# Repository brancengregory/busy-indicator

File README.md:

# Busy Indicator

A wireless status indicator system built with the XIAO ESP32C3. Designed for pairs who want to communicate their availability without interrupting each other's flow state.

## Overview

The Busy Indicator is a simple, elegant solution to a common problem: knowing when your partner or colleague is available without the social pressure of asking. Each device has two sets of red/green LEDs:

- **Local LEDs**: Show your current status (controlled by you)
- **Remote LEDs**: Show your partner's status (received wirelessly)

When your partner presses their button to change status, your remote LEDs update automatically via ESP-NOW wireless communication.

## Features

- **Dual Status Display**: Four LEDs total - two for your status, two for your partner's
- **Simple Controls**: Single button press toggles your status (red = busy, green = available)
- **Sleep Mode**: Long press (2 seconds) to enter light sleep for power saving
- **Wake on Button**: Press button to wake from sleep and resume operation
- **Wireless Sync**: ESP-NOW protocol provides instant status updates between devices
- **Visual Feedback**: Amber blinking confirms long press and wake events
- **Debounced Input**: Reliable button detection with 50ms debounce
- **Power Efficient**: Light sleep mode consumes minimal power when not in use

## Hardware

The PCB is designed around the Seeed Studio XIAO ESP32C3 with:

- **Microcontroller**: XIAO ESP32C3 (RISC-V, WiFi + Bluetooth)
- **LEDs**: 4x 3mm through-hole LEDs (2 red, 2 green)
- **Current limiting**: 4x axial resistors
- **Input**: 12mm push button
- **Power**: USB-C via XIAO board (or external battery via battery pads)

### GPIO Pinout

| Function | GPIO |
|----------|------|
| Local Red LED | GPIO3 |
| Local Green LED | GPIO4 |
| Remote Red LED | GPIO21 |
| Remote Green LED | GPIO20 |
| Button | GPIO10 |

### PCB Design Files

The hardware design is in KiCad 9.0 format:

- `hardware/busy-indicator/busy-indicator.kicad_sch` - Schematic
- `hardware/busy-indicator/busy-indicator.kicad_pcb` - PCB layout
- `hardware/busy-indicator/busy-indicator.kicad_pro` - Project settings
- `hardware/libs/XIAO_ESP32C3/` - XIAO ESP32C3 footprint and symbol library (git submodule)

## Firmware

The firmware is written in Rust using the Embassy async framework:

- **Language**: Rust (embedded no-std)
- **Framework**: Embassy (async/await for embedded)
- **HAL**: esp-hal for ESP32-C3
- **Networking**: esp-radio (ESP-NOW over WiFi)
- **Target**: riscv32imc-unknown-none-elf

### Architecture

The firmware uses an actor-model architecture with Embassy tasks:

1. **State Manager** (`state_manager`): Pure state machine handling all state transitions
2. **LED Controller** (`led_controller`): Handles LED output with retry logic
3. **Button Task** (`button_task`): Button debouncing, press detection, and sleep control
4. **ESP-NOW Task** (`esp_now_task`): Wireless communication between devices

### Key Components

- **ButtonHandler**: Debounced button input with short/long press detection
- **LedPair**: Abstraction for red/green LED pairs with color mixing (red + green = amber)
- **SystemState**: Tracks local status, remote status, and sleep state
- **Pure Transitions**: State changes are pure functions (no side effects), making testing easy

## Building

### Prerequisites

- Rust toolchain with `riscv32imc-unknown-none-elf` target
- `espflash` or `cargo-espflash` for flashing
- KiCad 9.0+ (for hardware modifications)

### Flashing Firmware

```bash
# Build and flash
cargo run --release

# Or flash pre-built binary
espflash flash target/riscv32imc-unknown-none-elf/release/busy-indicator
```

### Hardware Manufacturing

1. Open `hardware/busy-indicator/busy-indicator.kicad_pcb` in KiCad
2. Generate Gerber files for fabrication
3. Order PCBs from your preferred manufacturer (JLCPCB, PCBWay, etc.)
4. Solder components according to the schematic

## Usage

1. **Power on**: Both LED pairs will blink amber 3 times, then show red (default busy state)
2. **Toggle status**: Short press the button to switch between red (busy) and green (available)
3. **Check partner status**: Look at the "remote" LED pair - it mirrors your partner's device
4. **Enter sleep**: Long press the button (hold for 2 seconds until LEDs blink) to enter low-power mode
5. **Wake up**: Press the button to wake from sleep - LEDs will blink amber to confirm

### Wireless Pairing

Devices automatically discover each other via ESP-NOW broadcast on channel 11. No manual pairing required - just power on two devices within range and they'll sync automatically.

## Project Structure

```
busy-indicator/
├── src/
│   ├── bin/main.rs       # Firmware entry point and task definitions
│   └── lib.rs            # Library (currently empty, no_std marker)
├── hardware/
│   ├── busy-indicator/   # KiCad PCB design files
│   └── libs/             # Component libraries (XIAO_ESP32C3 submodule)
├── Cargo.toml            # Rust dependencies
├── build.rs              # Build script with helpful linker errors
└── .gitignore            # Git ignore patterns for Rust + KiCad
```

## License

This project is open source. See individual component licenses:
- Firmware: See LICENSE file in repository root
- XIAO_ESP32C3 library: See `hardware/libs/XIAO_ESP32C3/LICENSE`

## Acknowledgments

- [esp-hal](https://github.com/esp-rs/esp-hal) - Rust HAL for ESP microcontrollers
- [Embassy](https://github.com/embassy-rs/embassy) - Async/await framework for embedded
- [esp-radio](https://github.com/esp-rs/esp-radio) - WiFi/ESP-NOW support for ESP32
- [Seeed Studio](https://www.seeedstudio.com/) - XIAO ESP32C3 hardware

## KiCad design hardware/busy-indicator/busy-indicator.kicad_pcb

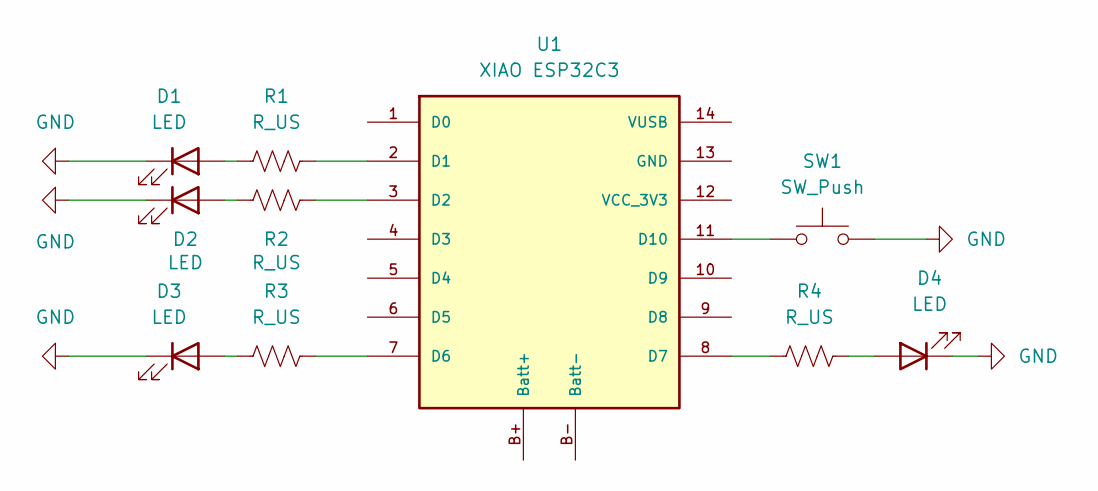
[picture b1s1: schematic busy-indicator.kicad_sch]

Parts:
D1, D2, D3, D4: LED; LED_D3.0mm
R1, R2, R3, R4: R_US; R_Axial_DIN0207_L6.3mm_D2.5mm_P10.16mm_Horizontal
SW1: SW_Push; SW_PUSH-12mm
U1: XIAO ESP32C3; xiao_esp32c3

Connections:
GND: D1.1 (K), D2.1 (K), D3.1 (K), D4.1 (K), SW1.2
unnamed: D1.2 (A), R1.1
unnamed: D2.2 (A), R2.1
unnamed: D3.2 (A), R3.2
unnamed: D4.2 (A), R4.2
unnamed: R1.2, U1.2 (D1)
unnamed: R2.2, U1.3 (D2)
unnamed: R3.1, U1.7 (D6)
unnamed: R4.1, U1.8 (D7)
unnamed: SW1.1, U1.11 (D10)

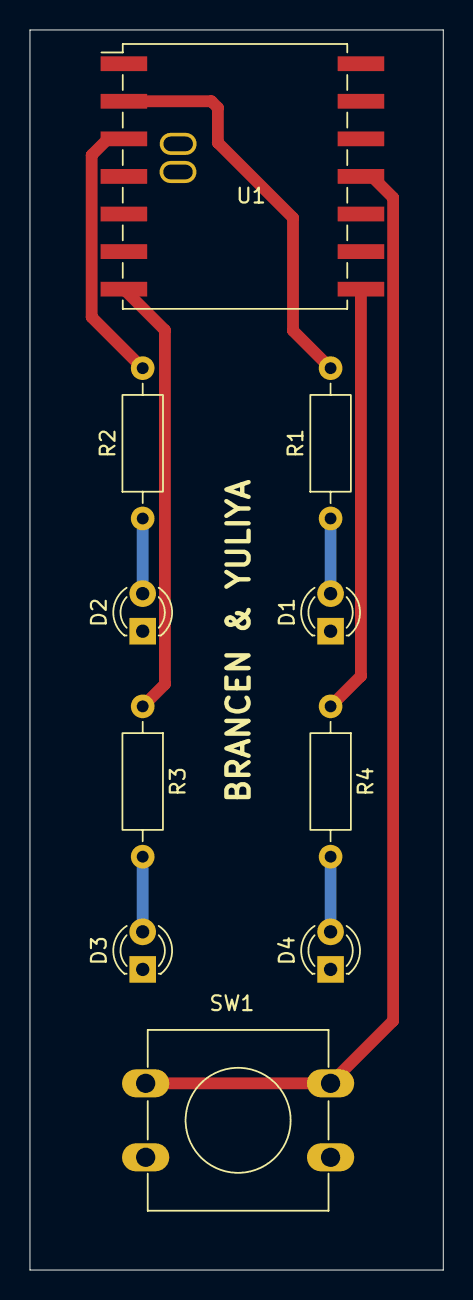
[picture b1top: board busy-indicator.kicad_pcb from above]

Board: 2 copper layers, 27.9 x 83.8 mm, 10 parts (0 on the bottom side), 10 nets.

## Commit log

2025-07-12 Init commit
2025-07-19 Working initial build
2025-07-19 Red/green led example
2025-07-20 Simplified program
2025-07-20 Add enclosure notes; update program to two color blink
2025-07-21 Demo wifi
2025-07-21 Successfully starting AP
2025-07-27 Simple led toggle
2026-01-29 init: led toggling button
2026-01-29 feat: add esp-now sync
    Implement ESP-NOW communication to synchronize state between devices.
    - Refactor to event-driven architecture with channels
    - Distinguish between short and long button presses
    - Add tasks for traffic light logic, button handling, and ESP-NOW
2026-01-29 chore: backup old files
2026-01-29 chore: update binary name
2026-01-29 chore: clippy and fmt
2026-01-29 feat: light sleep on button hold
2026-01-29 feat: blink lights on sleep and wake
2026-01-29 feat: move magic numbers into constants
2026-01-29 feat: flash both local leds on wake and sleep
    - increase debounce and wait on wake time
2026-01-29 refactor(led): introduce LedPair abstraction and consolidate effects
2026-01-30 feat: add ButtonHandler and fix WiFi/ESP-NOW wake recovery
2026-03-15 feat(hardware): add busy indicator pcb design files - add KiCad schematic, PCB layout, and project configuration - add XIAO ESP32C3 library as git submodule - add KiCad-specific patterns to .gitignor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
2026-03-15 chore: add readme
